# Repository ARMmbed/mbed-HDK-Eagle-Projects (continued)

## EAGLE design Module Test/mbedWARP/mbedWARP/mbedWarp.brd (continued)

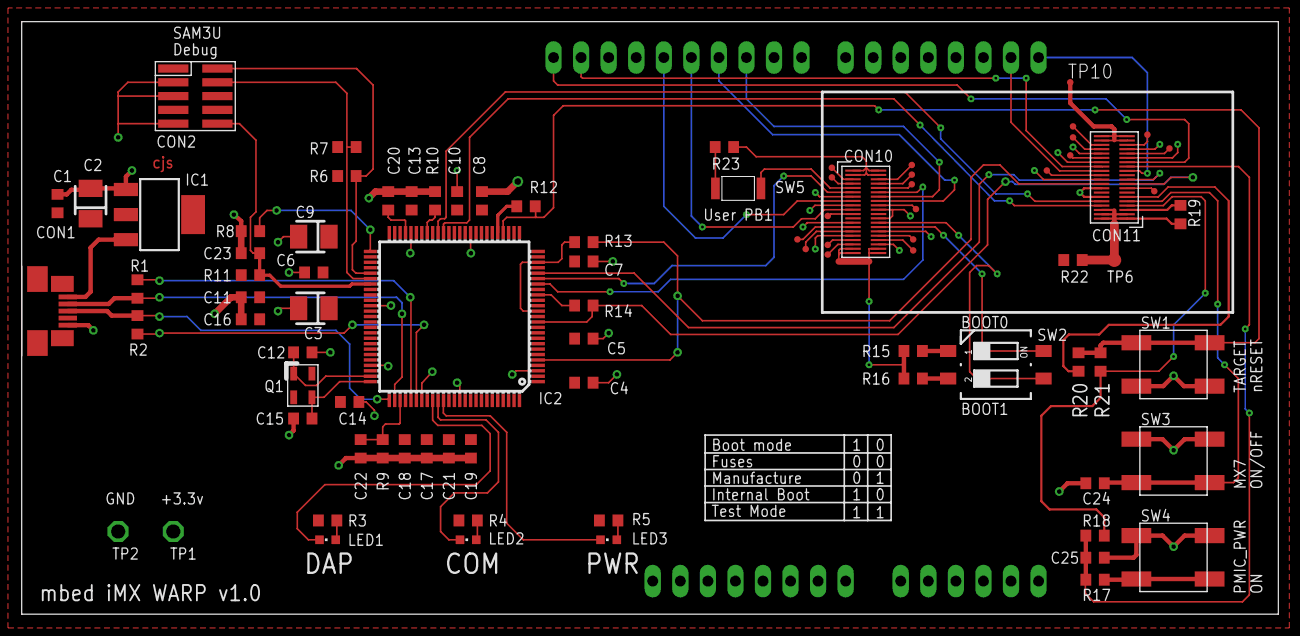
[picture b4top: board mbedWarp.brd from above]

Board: 2 copper layers, 115.8 x 54.6 mm, 88 parts (0 on the bottom side), 77 nets.

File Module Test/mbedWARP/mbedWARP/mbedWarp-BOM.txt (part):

Partlist exported from C:/Users/cstyles/Documents/mbed/Projects/AppsEng/mbed-HDK/Projects/treadstone/mbedWARP/mbedWARP/mbedWarp.sch at 09/10/2017 16:39

Qty Value              Device              Package             Parts                                                                                                            Description                                   MF   MFN        OC-DIGIKEY OC-MOUSER      OC-NEWARK TP_SIGNAL_NAME
1   0                  R0603               0603                R12                                                                                                                                                                                                                              
2   0R                 R0603               0603                R20, R21                                                                                                                                                                                                                         
1   0R                 RESISTOR0603        0603                R22                                                                                                              Resistor                                                                                                        
14  100nF              C0603               0603                C1, C4, C5, C7, C8, C10, C11, C13, C14, C16, C17, C18, C19, C21                                                  Capacitor                                                                                                       
2   100nF              CAPACITOR0603       0603                C24, C25                                                                                                         Capacitor                                                                                                       
1   10k                RESISTOR0603        0603                R19                                                                                                              Resistor                                                                                                        
2   10nF               C0603               0603                C6, C20                                                                                                          Capacitor                                                                                                       
2   10pF               C0603               0603                C22, C23                                                                                                         Capacitor                                                                                                       
3   10uF               C-POL_B             CASE-B              C2, C3, C9                                                                                                       Polarised capacitor                                                                                             
1   12MHz              Q_3.2X2.5           3.2X.2.5            Q1                                                                                                                                                                                                                               
2   150                R0603               0603                R13, R14                                                                                                                                                                                                                         
2   18pF               C0603               0603                C12, C15                                                                                                         Capacitor                                                                                                       
1   1k                 R0603               0603                R10                                                                                                                                                                                                                              
5   1k                 RESISTOR0603        0603                R15, R16, R17, R18, R23                                                                                          Resistor                                                                                                        
2   39R                R0603               0603                R1, R2                                                                                                                                                                                                                           
3   470R               R0603               0603                R3, R4, R5                                                                                                                                                                                                                       
4   4k7                R0603               0603                R6, R7, R8, R11                                                                                                                                                                                                                  
1   6k8                R0603               0603                R9                                                                                                                                                                                                                               
1   ARDUINO-R3_SILK    ARDUINO-R3_SILK     ARDUINO-R3-SILK     BRD1                                                                                                             Shield for Arduino R3                                                                                           
1   AT91SAM3U2CA       AT91SAM3U2CA        LQFP100             IC2                                                                                                                                                                                                                              
1   B2B1               DF40HC-XX-40DS-XX-V DF40HC-XX-40DS-XX-V CON10                                                                                                                                                                                                                            
1   B2B2               DF40HC-XX-40DS-XX-V DF40HC-XX-40DS-XX-V CON11                                                                                                                                                                                                                            
1   BLUE               LED0603             CHIPLED_0603        LED3                                                                                                             SMD LED                                                                                                         
1   DM-02              DM-02               DM-02               SW2                                                                                                                                                                                                                              
1   GREEN              LED0603             CHIPLED_0603        LED1                                                                                                             SMD LED                                                                                                         
1   LD1117S33          LD1117S33           SOT223              IC1                                                                                                              VOLTAGE REGULATOR SMD 3,3V                                                                                      
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
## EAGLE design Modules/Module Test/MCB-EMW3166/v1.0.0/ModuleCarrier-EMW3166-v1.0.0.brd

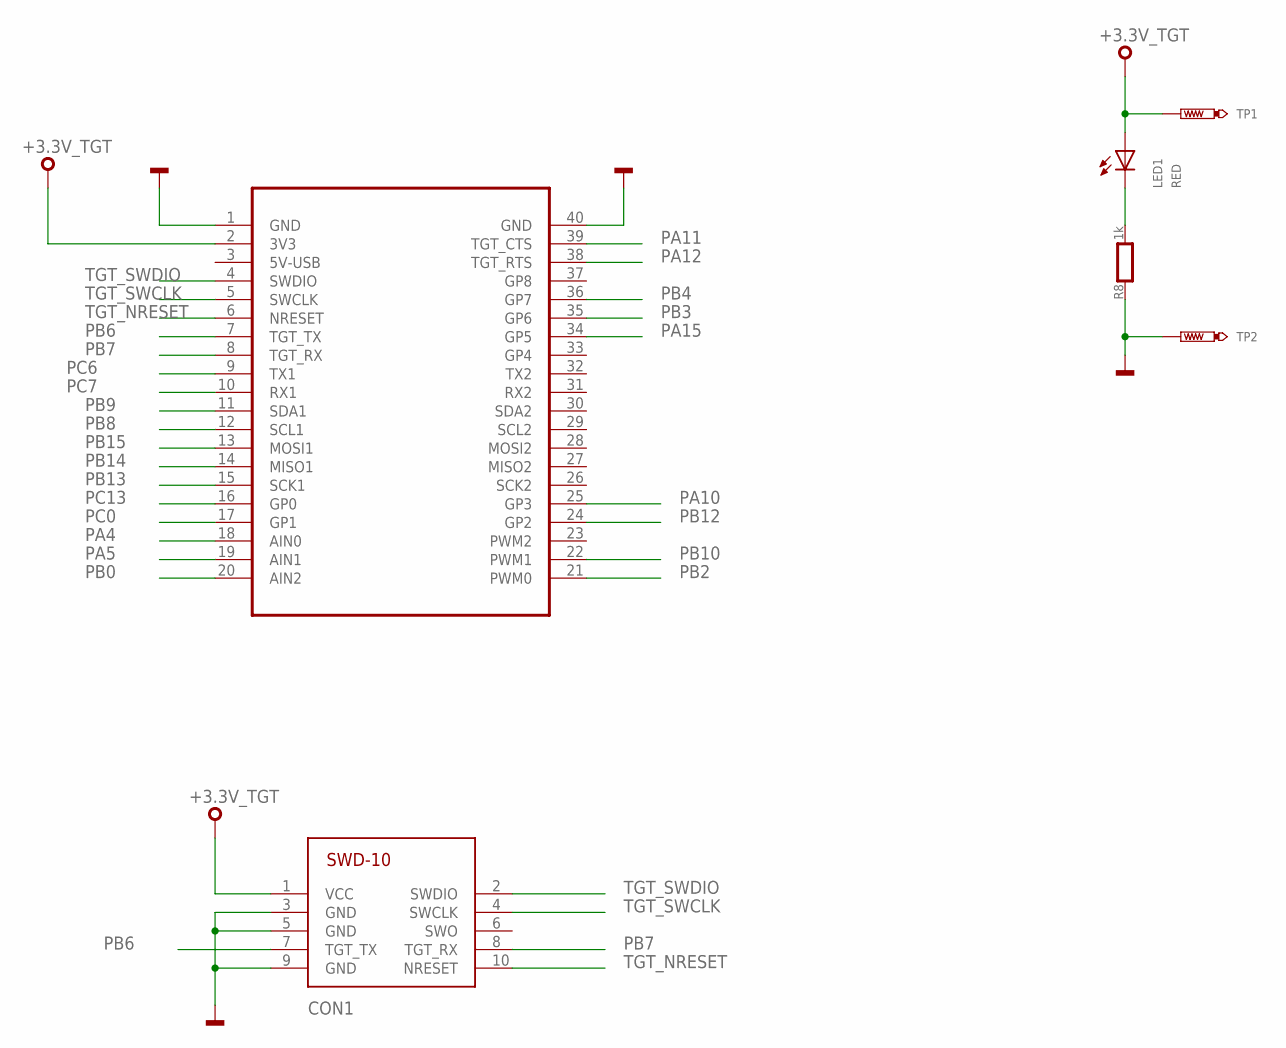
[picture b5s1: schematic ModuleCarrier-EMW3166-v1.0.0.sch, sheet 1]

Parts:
CON1: SWD-10/TC2050_SMD; FTSH-105-02
LED1: RED; CHIPLED_0603
R8: 1k; 0603
TP1, TP2: TEST-POINT-50R-PTH; TP50-PTH
U$1: MODULE_DAUGHTER

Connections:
+3.3V_TGT: CON1.1 (VCC), LED1.A, TP1.TP, U$1.2 (3V3); also elsewhere on the board
GND: CON1.3 (GND), CON1.5 (GND), CON1.9 (GND), R8.1, TP2.TP, U$1.1 (GND), U$1.40 (GND); also elsewhere on the board
PA4: U$1.18 (AIN0); also elsewhere on the board
PA5: U$1.19 (AIN1); also elsewhere on the board
PA10: U$1.25 (GP3); also elsewhere on the board
PA11: U$1.39 (TGT_CTS); also elsewhere on the board
PA12: U$1.38 (TGT_RTS); also elsewhere on the board
PA15: U$1.34 (GP5); also elsewhere on the board
PA_1: LED1.C, R8.2
PB0: U$1.20 (AIN2); also elsewhere on the board
PB2: U$1.21 (PWM0); also elsewhere on the board
PB3: U$1.35 (GP6); also elsewhere on the board
PB4: U$1.36 (GP7); also elsewhere on the board
PB6: CON1.7 (TGT_TX), U$1.7 (TGT_TX); also elsewhere on the board
PB7: CON1.8 (TGT_RX), U$1.8 (TGT_RX); also elsewhere on the board
PB8: U$1.12 (SCL1); also elsewhere on the board
PB9: U$1.11 (SDA1); also elsewhere on the board
PB10: U$1.22 (PWM1); also elsewhere on the board
PB12: U$1.24 (GP2); also elsewhere on the board
PB13: U$1.15 (SCK1); also elsewhere on the board
PB14: U$1.14 (MISO1); also elsewhere on the board
PB15: U$1.13 (MOSI1); also elsewhere on the board
PC0: U$1.17 (GP1); also elsewhere on the board
PC6: U$1.9 (TX1); also elsewhere on the board
PC7: U$1.10 (RX1); also elsewhere on the board
PC13: U$1.16 (GP0); also elsewhere on the board
TGT_NRESET: CON1.10 (NRESET), U$1.6 (NRESET); also elsewhere on the board
TGT_SWCLK: CON1.4 (SWCLK), U$1.5 (SWCLK); also elsewhere on the board
TGT_SWDIO: CON1.2 (SWDIO), U$1.4 (SWDIO); also elsewhere on the board

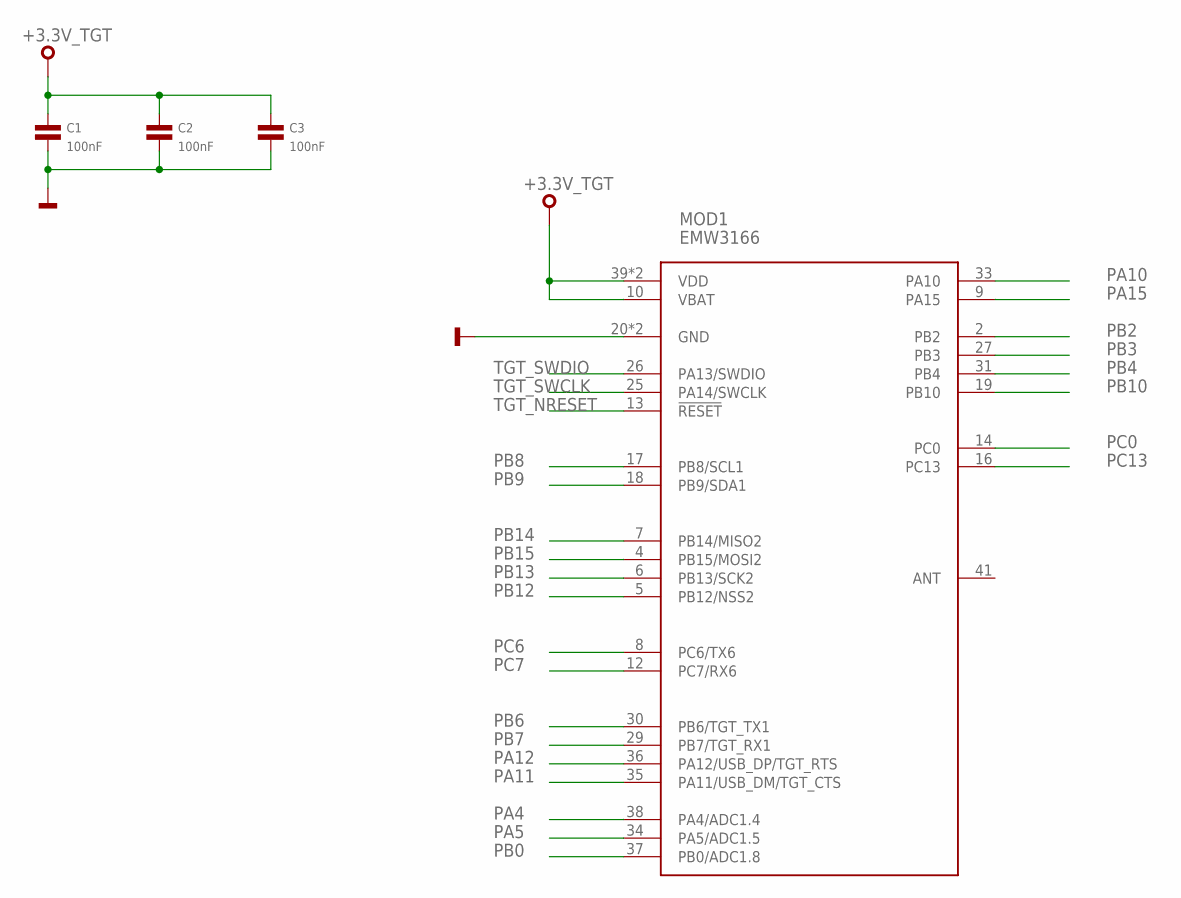
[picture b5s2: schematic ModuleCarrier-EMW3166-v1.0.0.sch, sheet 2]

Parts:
C1, C2, C3: 100nF; 0603
MOD1: EMW3166

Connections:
+3.3V_TGT: C1.1, C2.1, C3.1, MOD1.10 (VBAT), MOD1.39 (VDD), MOD1.40 (VDD); also elsewhere on the board
GND: C1.2, C2.2, C3.2, MOD1.20 (GND), MOD1.21 (GND); also elsewhere on the board
PA4: MOD1.38 (PA4/ADC1.4); also elsewhere on the board
PA5: MOD1.34 (PA5/ADC1.5); also elsewhere on the board
PA10: MOD1.33 (PA10); also elsewhere on the board
PA11: MOD1.35 (PA11/USB_DM/TGT_CTS); also elsewhere on the board
PA12: MOD1.36 (PA12/USB_DP/TGT_RTS); also elsewhere on the board
PA15: MOD1.9 (PA15); also elsewhere on the board
PB0: MOD1.37 (PB0/ADC1.8); also elsewhere on the board
PB2: MOD1.2 (PB2); also elsewhere on the board
PB3: MOD1.27 (PB3); also elsewhere on the board
PB4: MOD1.31 (PB4); also elsewhere on the board
PB6: MOD1.30 (PB6/TGT_TX1); also elsewhere on the board
PB7: MOD1.29 (PB7/TGT_RX1); also elsewhere on the board
PB8: MOD1.17 (PB8/SCL1); also elsewhere on the board
PB9: MOD1.18 (PB9/SDA1); also elsewhere on the board
PB10: MOD1.19 (PB10); also elsewhere on the board
PB12: MOD1.5 (PB12/NSS2); also elsewhere on the board
PB13: MOD1.6 (PB13/SCK2); also elsewhere on the board
PB14: MOD1.7 (PB14/MISO2); also elsewhere on the board
PB15: MOD1.4 (PB15/MOSI2); also elsewhere on the board
PC0: MOD1.14 (PC0); also elsewhere on the board
PC6: MOD1.8 (PC6/TX6); also elsewhere on the board
PC7: MOD1.12 (PC7/RX6); also elsewhere on the board
PC13: MOD1.16 (PC13); also elsewhere on the board
TGT_NRESET: MOD1.13 (!RESET); also elsewhere on the board
TGT_SWCLK: MOD1.25 (PA14/SWCLK); also elsewhere on the board
TGT_SWDIO: MOD1.26 (PA13/SWDIO); also elsewhere on the board

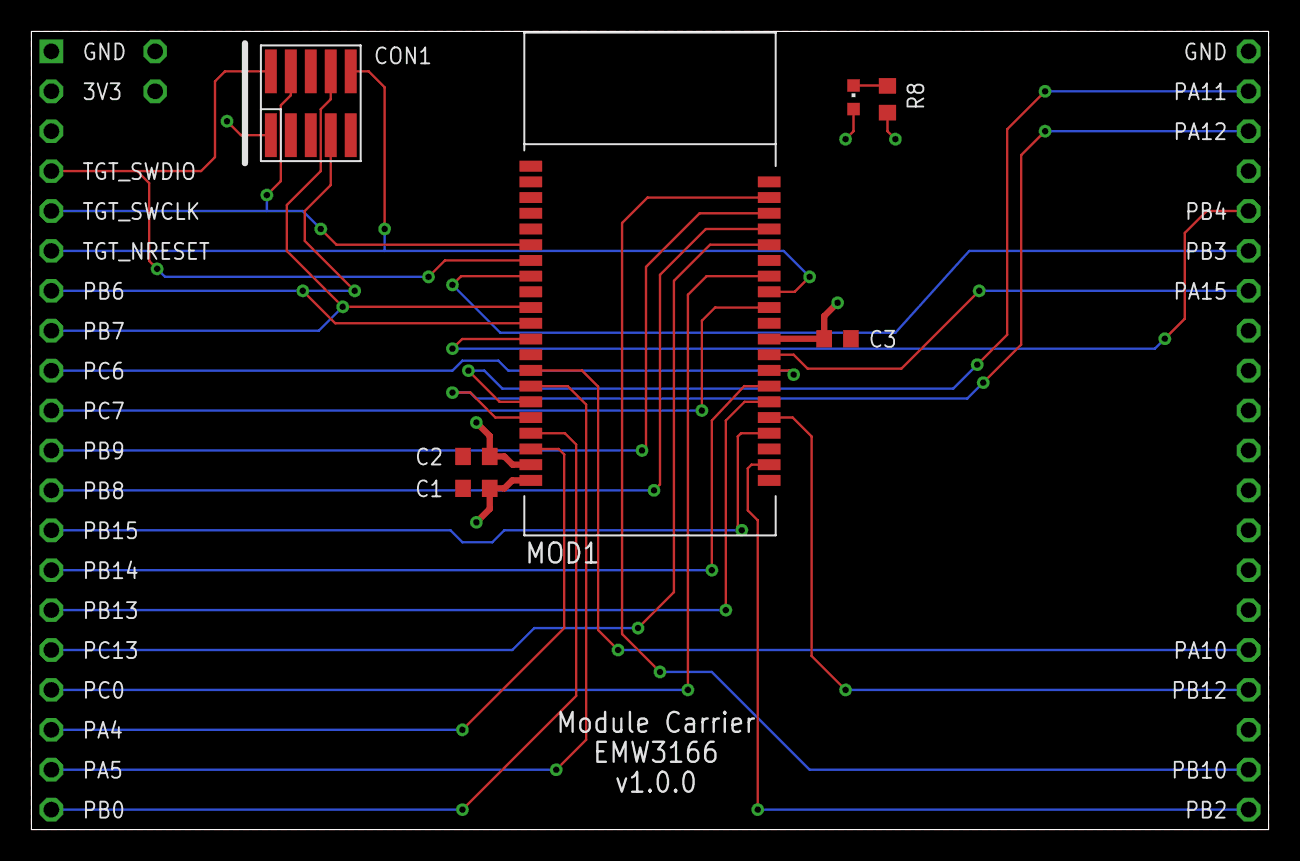
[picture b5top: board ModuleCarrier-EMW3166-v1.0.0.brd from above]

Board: 2 copper layers, 78.7 x 50.8 mm, 10 parts (0 on the bottom side), 29 nets.

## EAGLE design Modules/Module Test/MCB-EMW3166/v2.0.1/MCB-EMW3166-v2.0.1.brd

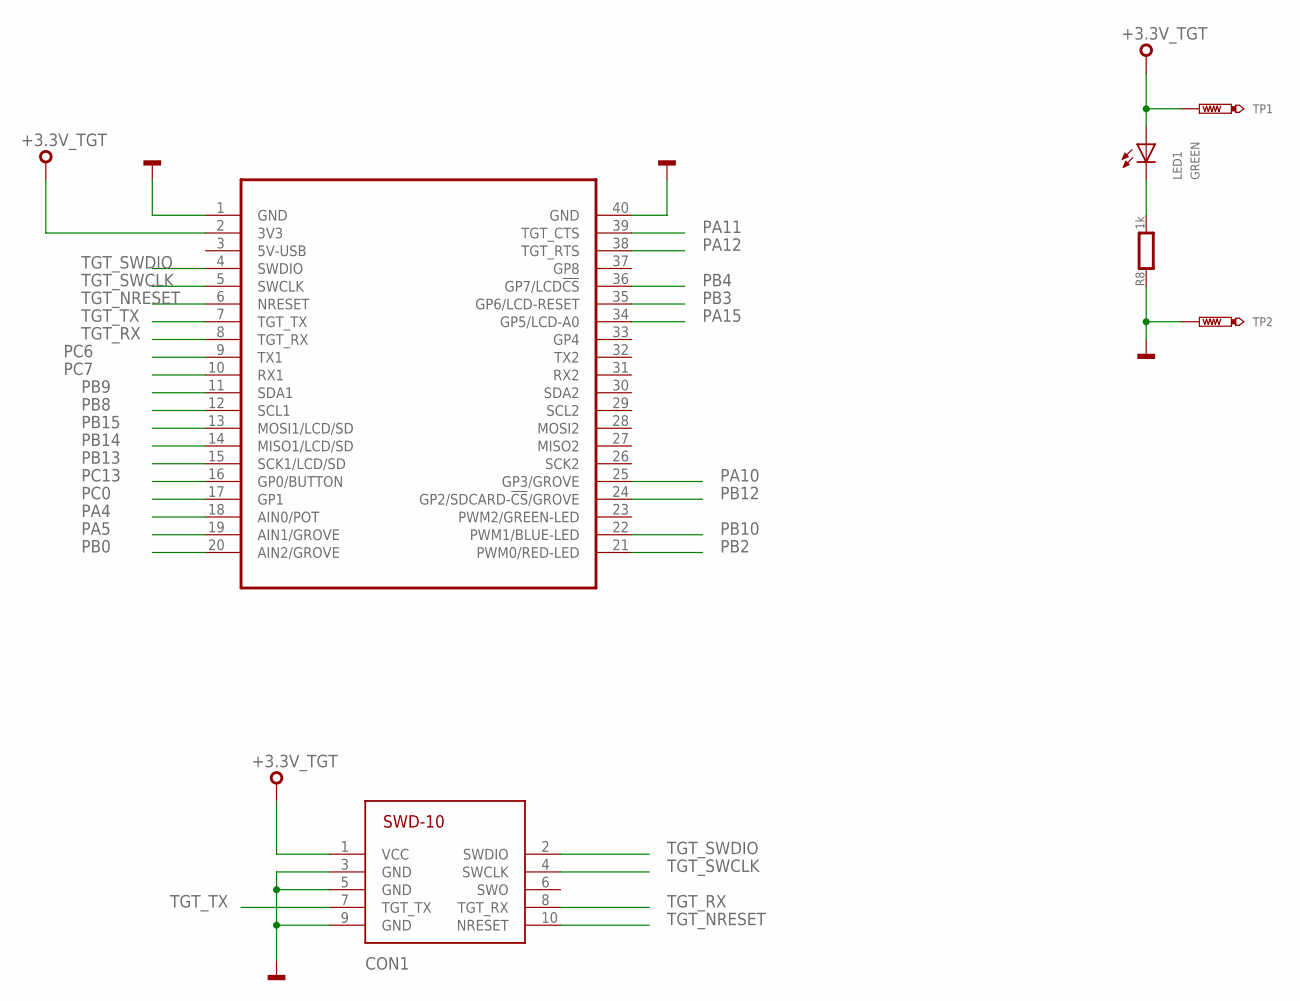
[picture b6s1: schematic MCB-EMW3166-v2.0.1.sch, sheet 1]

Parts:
CON1: SWD-10/TC2050_SMD; FTSH-105-02
LED1: GREEN; CHIPLED_0603
MOD2: MODULE_DAUGHTER
R8: 1k; 0603
TP1, TP2: TEST_POINT-50R-PTH; TP50-PTH

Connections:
+3.3V_TGT: CON1.1 (VCC), LED1.A, MOD2.2 (3V3), TP1.TP; also elsewhere on the board
GND: CON1.3 (GND), CON1.5 (GND), CON1.9 (GND), MOD2.1 (GND), MOD2.40 (GND), R8.1, TP2.TP; also elsewhere on the board
PA4: MOD2.18 (AIN0/POT); also elsewhere on the board
PA5: MOD2.19 (AIN1/GROVE); also elsewhere on the board
PA10: MOD2.25 (GP3/GROVE); also elsewhere on the board
PA11: MOD2.39 (TGT_CTS); also elsewhere on the board
PA12: MOD2.38 (TGT_RTS); also elsewhere on the board
PA15: MOD2.34 (GP5/LCD-A0); also elsewhere on the board
PA_1: LED1.C, R8.2
PB0: MOD2.20 (AIN2/GROVE); also elsewhere on the board
PB2: MOD2.21 (PWM0/RED-LED); also elsewhere on the board
PB3: MOD2.35 (GP6/LCD-RESET); also elsewhere on the board
PB4: MOD2.36 (GP7/LCD!CS); also elsewhere on the board
PB8: MOD2.12 (SCL1); also elsewhere on the board
PB9: MOD2.11 (SDA1); also elsewhere on the board
PB10: MOD2.22 (PWM1/BLUE-LED); also elsewhere on the board
PB12: MOD2.24 (GP2/SDCARD-!CS!/GROVE); also elsewhere on the board
PB13: MOD2.15 (SCK1/LCD/SD); also elsewhere on the board
PB14: MOD2.14 (MISO1/LCD/SD); also elsewhere on the board
PB15: MOD2.13 (MOSI1/LCD/SD); also elsewhere on the board
PC0: MOD2.17 (GP1); also elsewhere on the board
PC6: MOD2.9 (TX1); also elsewhere on the board
PC7: MOD2.10 (RX1); also elsewhere on the board
PC13: MOD2.16 (GP0/BUTTON); also elsewhere on the board
TGT_NRESET: CON1.10 (NRESET), MOD2.6 (NRESET); also elsewhere on the board
TGT_RX: CON1.8 (TGT_RX), MOD2.8 (TGT_RX); also elsewhere on the board
TGT_SWCLK: CON1.4 (SWCLK), MOD2.5 (SWCLK); also elsewhere on the board
TGT_SWDIO: CON1.2 (SWDIO), MOD2.4 (SWDIO); also elsewhere on the board
TGT_TX: CON1.7 (TGT_TX), MOD2.7 (TGT_TX); also elsewhere on the board

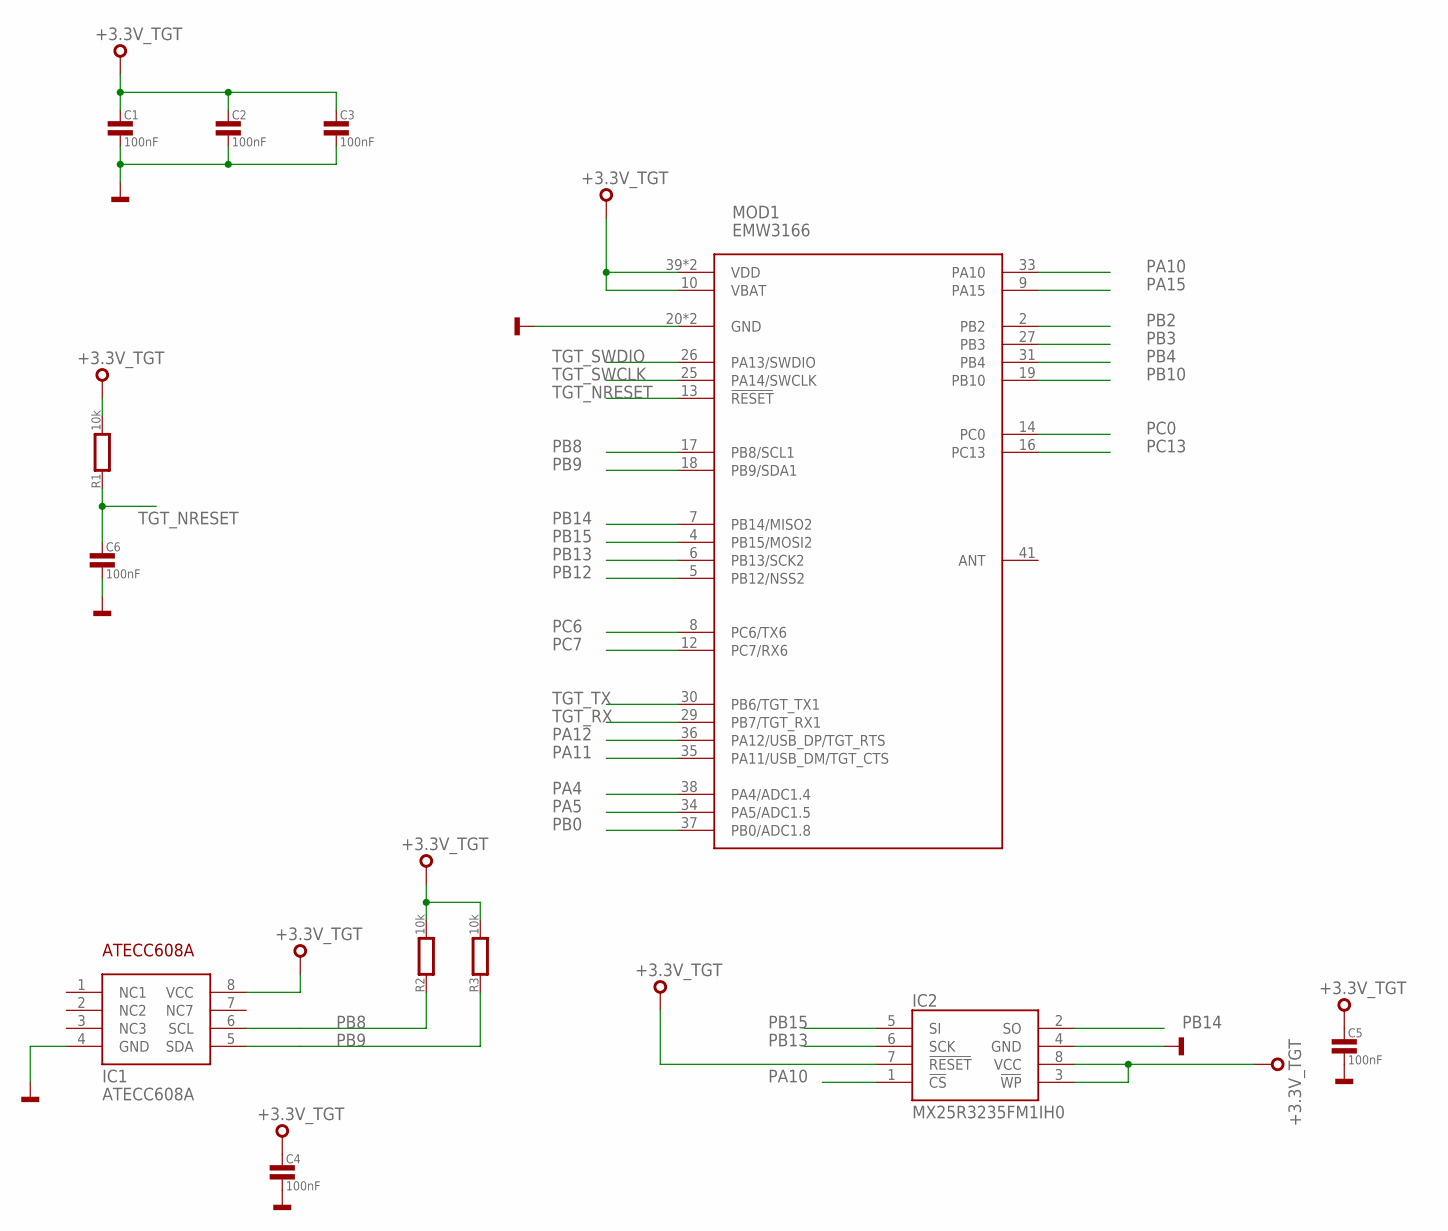
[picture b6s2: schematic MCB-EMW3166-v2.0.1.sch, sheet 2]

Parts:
C1, C2, C3, C4, C5, C6: 100nF; 0603
IC1: ATECC608A; SO8
IC2: MX25R3235FM1IH0; SO8
MOD1: EMW3166
R1, R2, R3: 10k; 0603

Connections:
+3.3V_TGT: C1.1, C2.1, C3.1, C4.1, C5.1, IC1.8 (VCC), IC2.3 (!WP), IC2.7 (!RESET), IC2.8 (VCC), MOD1.10 (VBAT), MOD1.39 (VDD), MOD1.40 (VDD), R1.2, R2.2, R3.2; also elsewhere on the board
GND: C1.2, C2.2, C3.2, C4.2, C5.2, C6.2, IC1.4 (GND), IC2.4 (GND), MOD1.20 (GND), MOD1.21 (GND); also elsewhere on the board
PA4: MOD1.38 (PA4/ADC1.4); also elsewhere on the board
PA5: MOD1.34 (PA5/ADC1.5); also elsewhere on the board
PA10: IC2.1 (!CS), MOD1.33 (PA10); also elsewhere on the board
PA11: MOD1.35 (PA11/USB_DM/TGT_CTS); also elsewhere on the board
PA12: MOD1.36 (PA12/USB_DP/TGT_RTS); also elsewhere on the board
PA15: MOD1.9 (PA15); also elsewhere on the board
PB0: MOD1.37 (PB0/ADC1.8); also elsewhere on the board
PB2: MOD1.2 (PB2); also elsewhere on the board
PB3: MOD1.27 (PB3); also elsewhere on the board
PB4: MOD1.31 (PB4); also elsewhere on the board
PB8: IC1.6 (SCL), MOD1.17 (PB8/SCL1), R2.1; also elsewhere on the board
PB9: IC1.5 (SDA), MOD1.18 (PB9/SDA1), R3.1; also elsewhere on the board
PB10: MOD1.19 (PB10); also elsewhere on the board
PB12: MOD1.5 (PB12/NSS2); also elsewhere on the board
PB13: IC2.6 (SCK), MOD1.6 (PB13/SCK2); also elsewhere on the board
PB14: IC2.2 (SO), MOD1.7 (PB14/MISO2); also elsewhere on the board
PB15: IC2.5 (SI), MOD1.4 (PB15/MOSI2); also elsewhere on the board
PC0: MOD1.14 (PC0); also elsewhere on the board
PC6: MOD1.8 (PC6/TX6); also elsewhere on the board
PC7: MOD1.12 (PC7/RX6); also elsewhere on the board
PC13: MOD1.16 (PC13); also elsewhere on the board
TGT_NRESET: C6.1, MOD1.13 (!RESET), R1.1; also elsewhere on the board
TGT_RX: MOD1.29 (PB7/TGT_RX1); also elsewhere on the board
TGT_SWCLK: MOD1.25 (PA14/SWCLK); also elsewhere on the board
TGT_SWDIO: MOD1.26 (PA13/SWDIO); also elsewhere on the board
TGT_TX: MOD1.30 (PB6/TGT_TX1); also elsewhere on the board

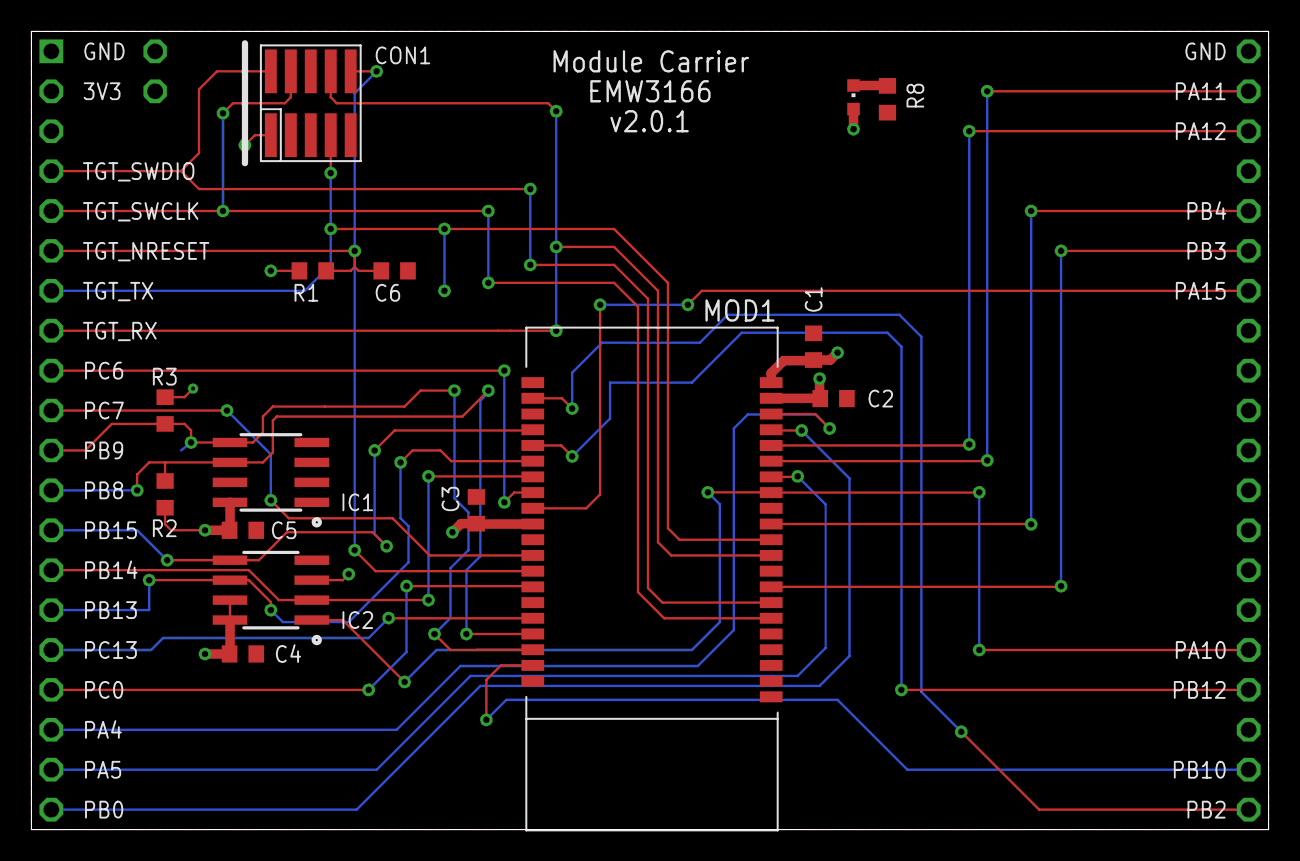
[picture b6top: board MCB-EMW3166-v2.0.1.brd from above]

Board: 2 copper layers, 78.7 x 50.8 mm, 18 parts (0 on the bottom side), 29 nets.

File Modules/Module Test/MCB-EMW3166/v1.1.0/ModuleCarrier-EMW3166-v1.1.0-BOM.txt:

Partlist exported from C:/Users/cstyles/Documents/mbed/Projects/blackbriar/ModuleCarrier-EMW3166/v1.1.0/ModuleCarrier-EMW3166-v1.1.0.sch at 07/12/2017 09:43

Qty Value              Device             Package         Parts                  Description                                                                                          
6   100nF              CAPACITOR0603      0603            C1, C2, C3, C4, C5, C6 Capacitor                                                                                            
1   10k                RESISTOR0603       0603            R1                     Resistor                                                                                             
1   1k                 RESISTOR0603       0603            R8                     Resistor                                                                                             
1   ATECC608A          ATECC608A          SO8             IC1                                                                                                                         
1   EMW3166            EMW3166            EMW3166         MOD1                                                                                                                        
1   MODULE_DAUGHTER    MODULE_DAUGHTER    MODULE_DAUGHTER U$1                                                                                                                         
1   MX25R3235FM1IH0    MX25R3235FM1IH0    SO8             IC2                    Serial Flash 32 Mb 80 Mhz                                                                            
1   RED                SMD_LED0603        CHIPLED_0603    LED1                   LED SMD, Colour Red                                                                                  
1   SWD-10/TC2050_SMD  SWD-10/TC2050_SMD  FTSH-105-02     CON1                   1mm pitch 10-Pin Cortex Programming Header with optional TC2050 footprint solderless interchangeable 
2   TEST-POINT-50R-PTH TEST-POINT-50R-PTH TP50-PTH        TP1, TP2
